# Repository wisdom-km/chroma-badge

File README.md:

# chroma-badge（BADGE-42C）：4.2 寸四色墨水屏 NFC 工牌

> **当前：** [状态](docs/06-current-status.md) · [交接](docs/03-handoff.md) · [流程](docs/09-process.md)（许可证 / CI / 贴胶 / 生产包）。2026-09-14 复审是**旧 564 段板**档案，不要当现板。

仓库：https://github.com/wisdom-km/chroma-badge

一块 **6.3 mm 厚**的电子工牌：4.2" 黑白红黄四色墨水屏 + ESP32-C3（Wi-Fi/BLE/原生 USB）+ ST25DV64KC NFC + ≤2 mm 超薄锂电 + USB-C。固件目前是 v0.2 上电自检；手机传图（F2）未写。

| 背面 PCB 渲染 | 外壳（FreeCAD） |
|---|---|
|  | 见 `hardware/enclosure/output/badge_assembly.step` |

## 在本地接着做

```bash
git clone https://github.com/wisdom-km/chroma-badge.git
cd chroma-badge
```

用 Cursor **打开这个文件夹**（本地 Agent）。根目录 `AGENTS.md` 和 `.cursor/rules/badge.mdc` 会带上约定。

## 仓库

- `LICENSE.md`：硬件 CERN-OHL-P-2.0，固件/脚本 MIT
- `AGENTS.md`：硬性约定与当前进度
- `docs/01-architecture-decisions.md`：选型
- `docs/02-bom-and-cost.md`：BOM；屏贴胶 3M 467MP
- `docs/03-handoff.md`：复现步骤与**当前板**指纹
- `docs/09-process.md`：CI、生产包、贴胶
- `hardware/pcb/`：由 `scripts/design.py` 生成
- `firmware/README.md`：v0.2 自检；不要覆盖 `output/badge-42c-v0.1*.bin`

## 快速开始

全量 ERC/DRC 需要 KiCad **10.0.6**。不要把 `gen_pcb.py` 当日常命令（会清布线）。日常检查：

```bash
cd hardware/pcb
python3 scripts/check_netlist.py
./scripts/export.sh --check-only
```

自动布线流程见 `docs/03-handoff.md` 第 3 节。

## 状态

**H2（2026-09-15）：** 58 封装，PCB **680 段 / 115 过孔**，J1.7 NC。KiCad 10.0.6 全量 ERC/DRC 0。USB **0.8 mm**。固件 **v0.2 F1**。没有生产 zip。

下一步：打样实机；F2 须选定一条传图路线。

## 第三方内容

- 乐鑫 KiCad 库（ESP32-C3-MINI-1）：CC-BY-SA 4.0
- HRO TYPE-C-31-M-14 封装：jenschr/USB-C-Connectors，公有领域
- 其余符号/封装来自 KiCad 官方库

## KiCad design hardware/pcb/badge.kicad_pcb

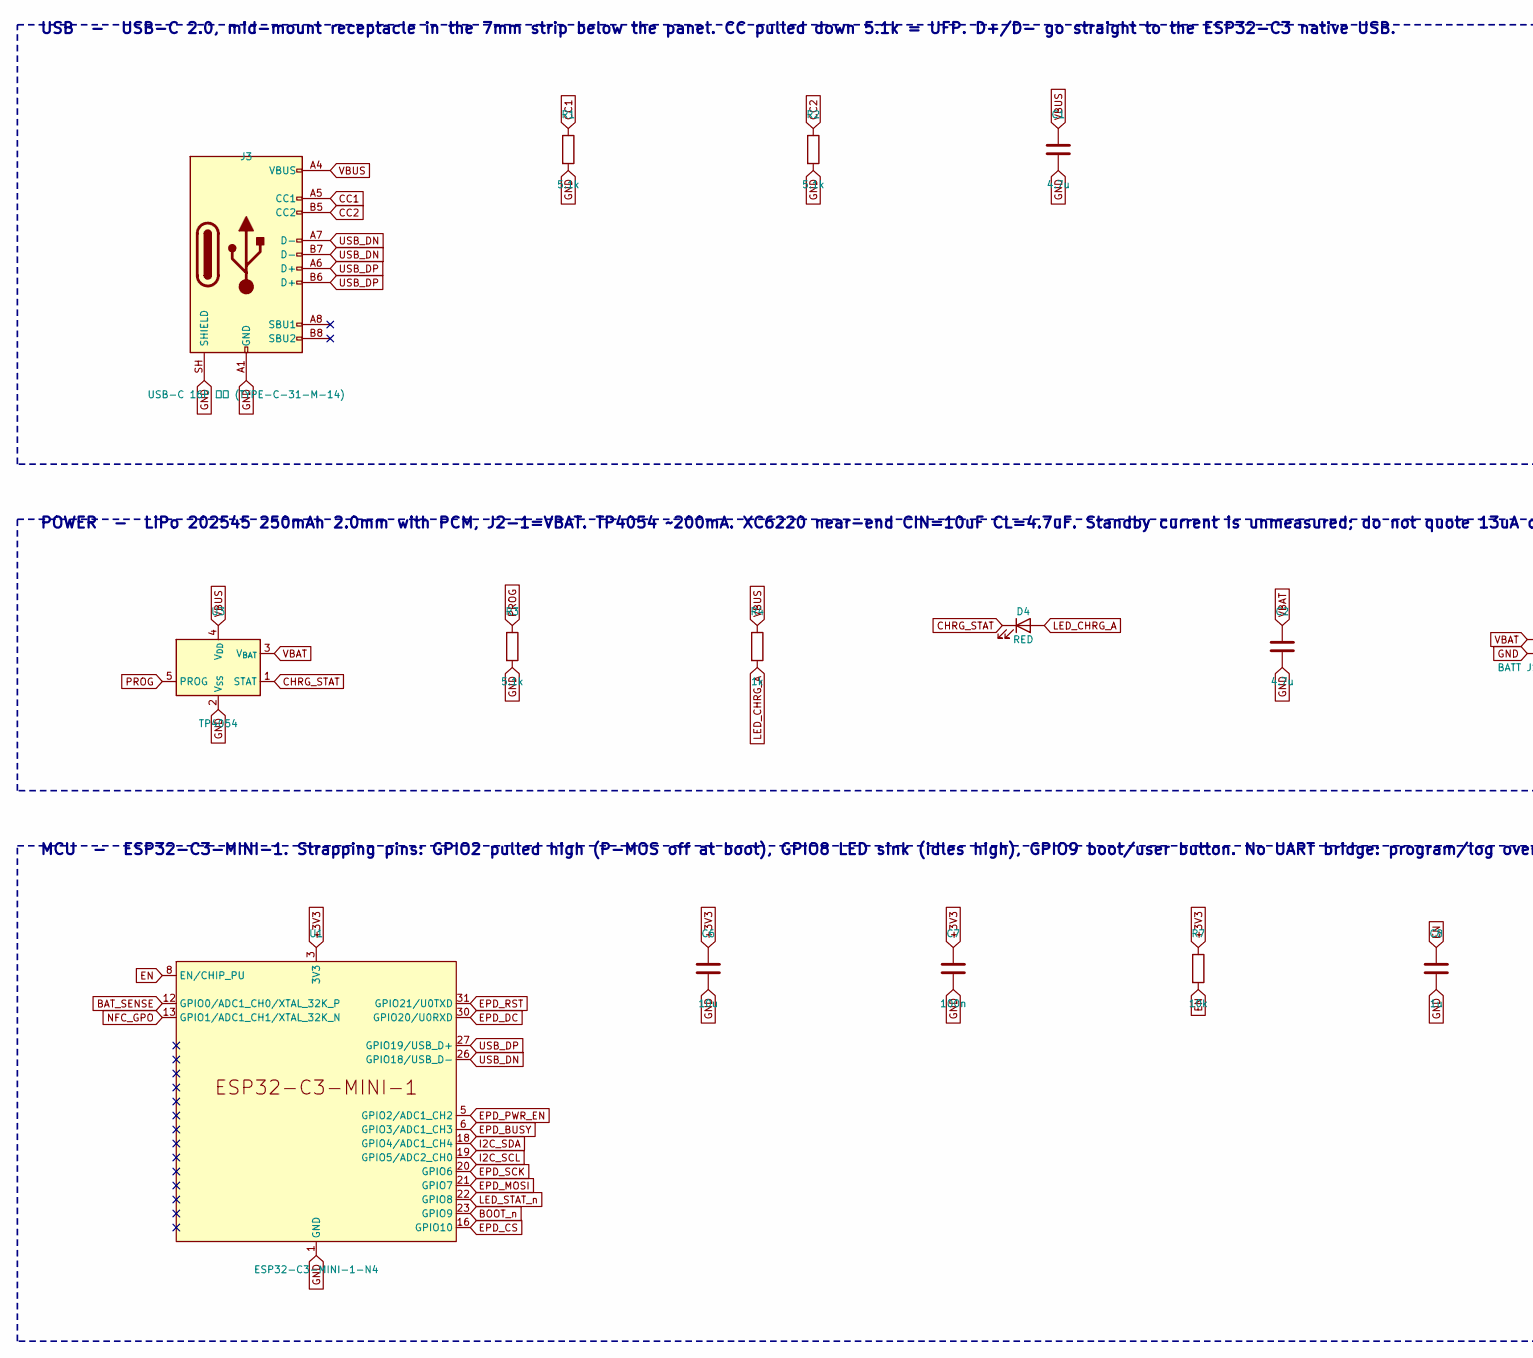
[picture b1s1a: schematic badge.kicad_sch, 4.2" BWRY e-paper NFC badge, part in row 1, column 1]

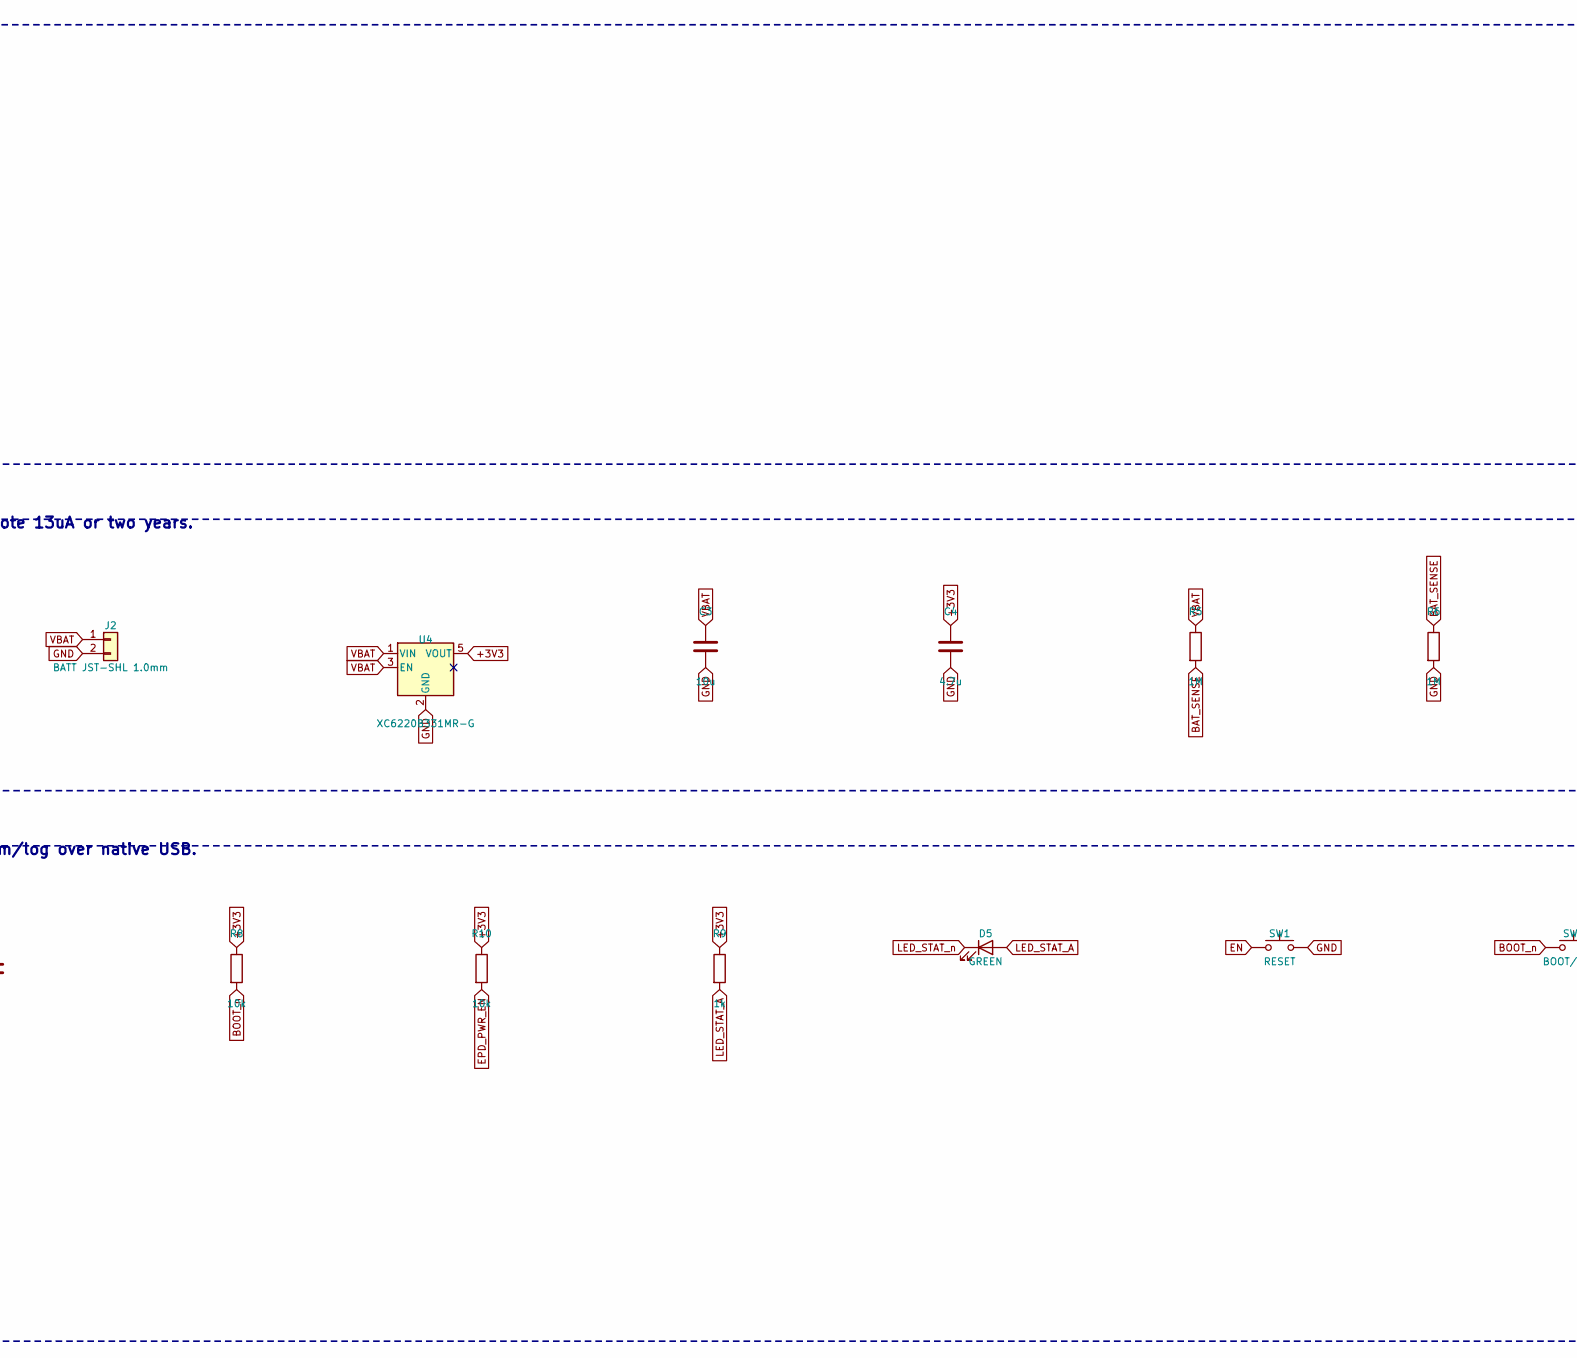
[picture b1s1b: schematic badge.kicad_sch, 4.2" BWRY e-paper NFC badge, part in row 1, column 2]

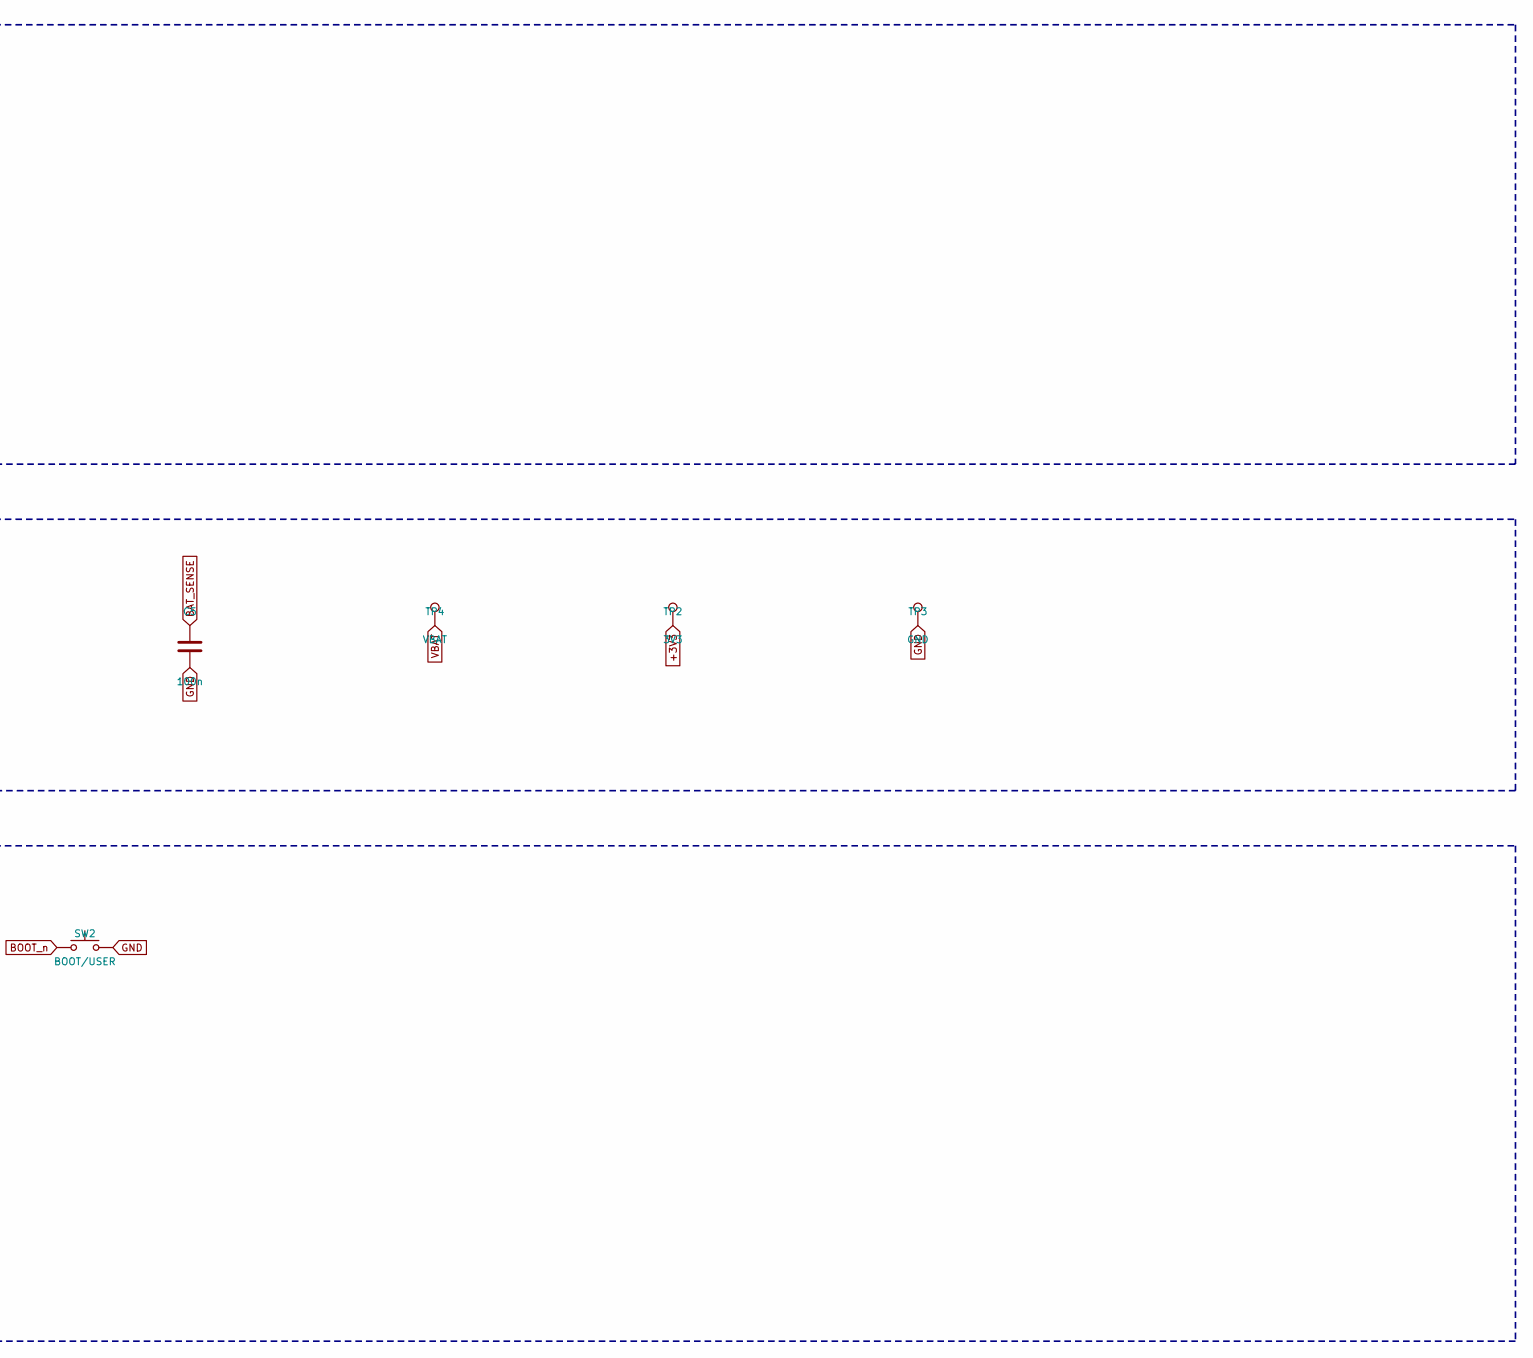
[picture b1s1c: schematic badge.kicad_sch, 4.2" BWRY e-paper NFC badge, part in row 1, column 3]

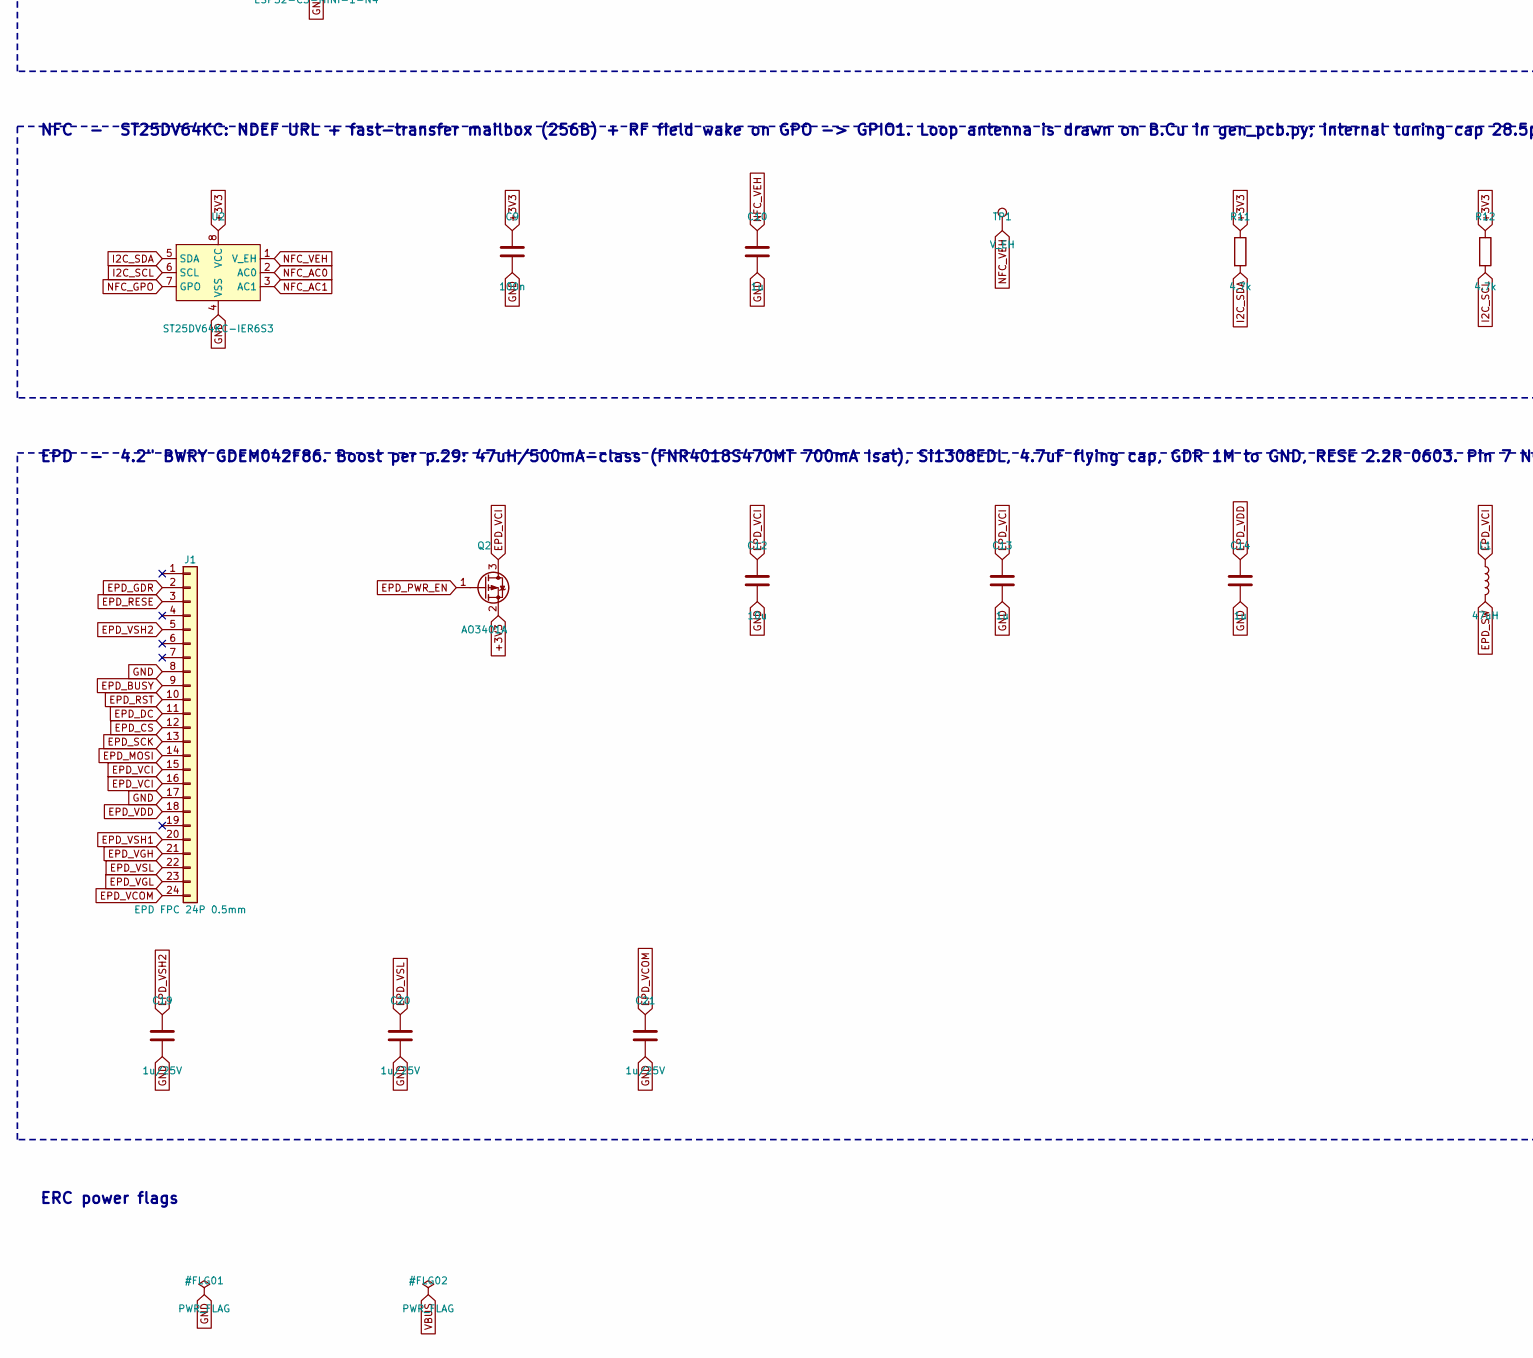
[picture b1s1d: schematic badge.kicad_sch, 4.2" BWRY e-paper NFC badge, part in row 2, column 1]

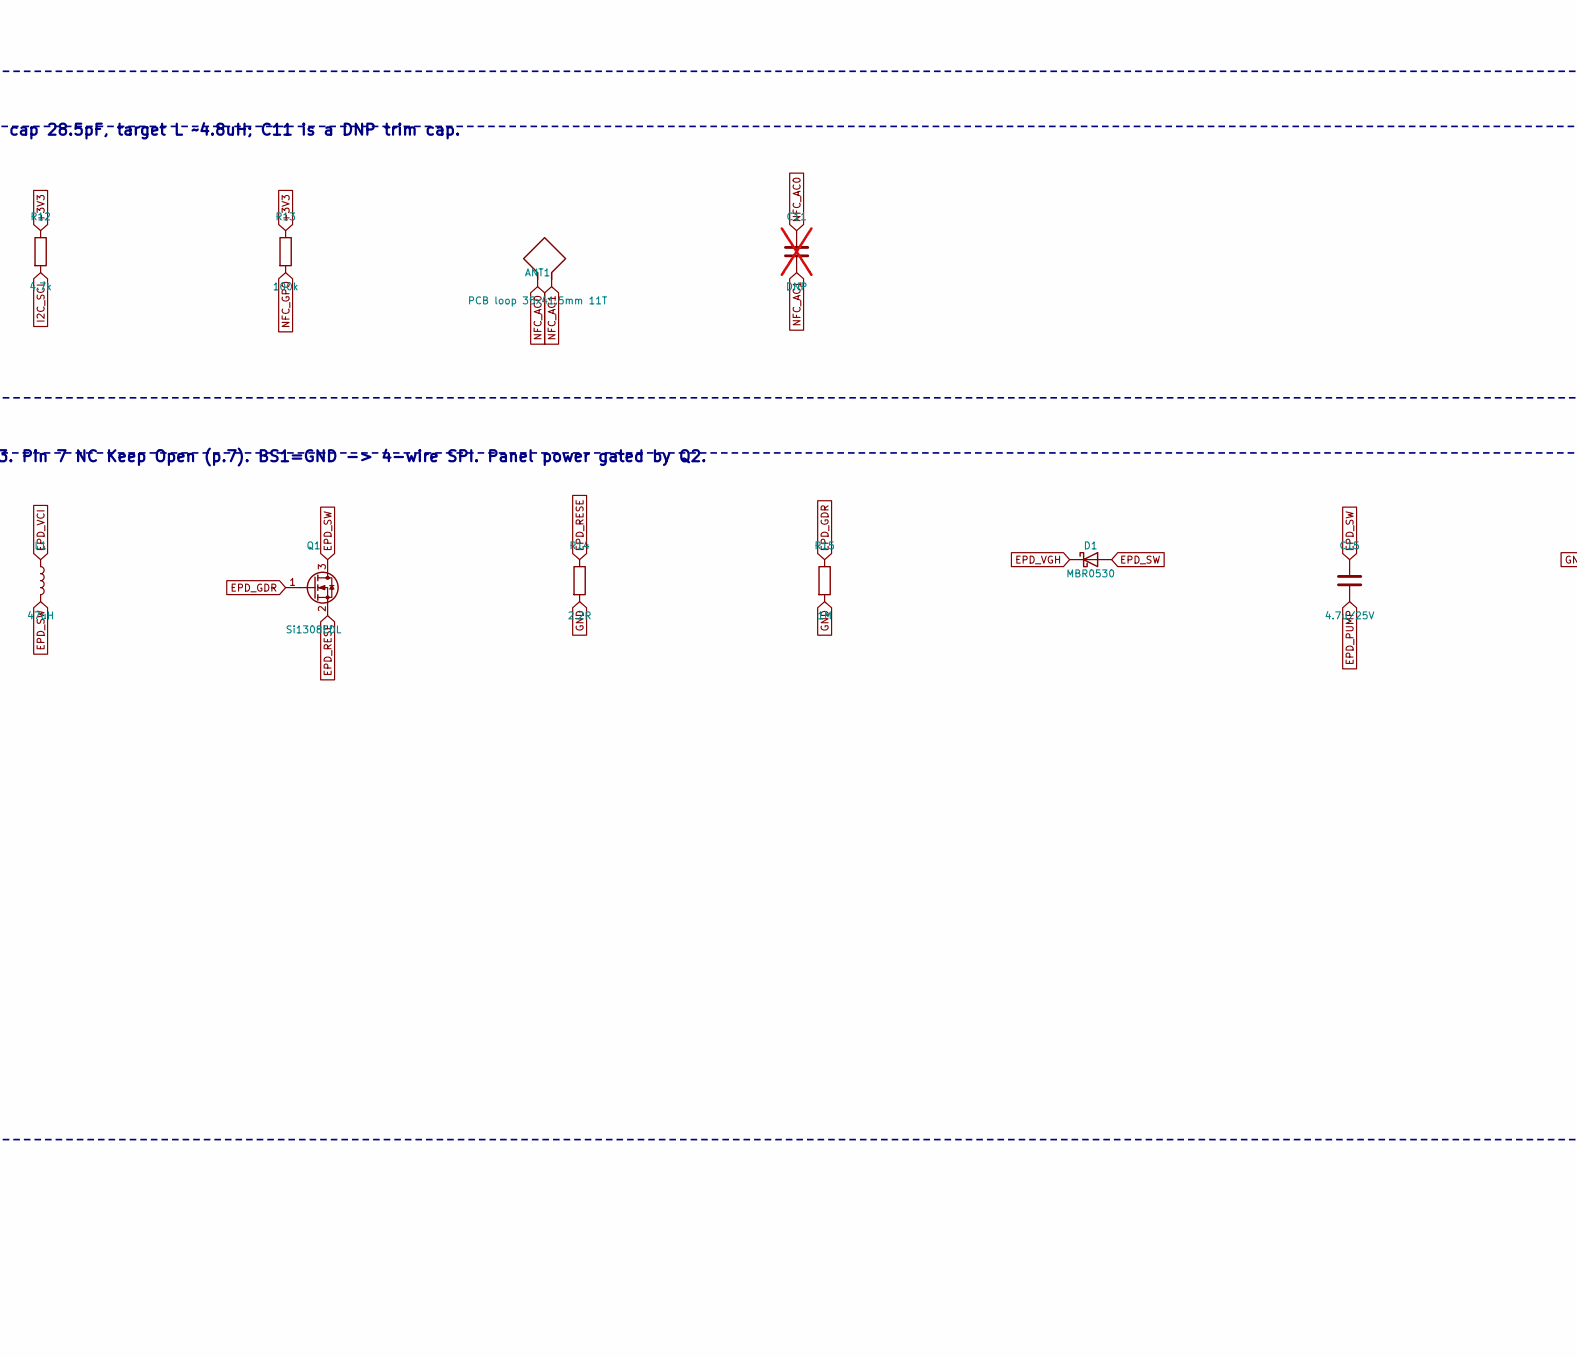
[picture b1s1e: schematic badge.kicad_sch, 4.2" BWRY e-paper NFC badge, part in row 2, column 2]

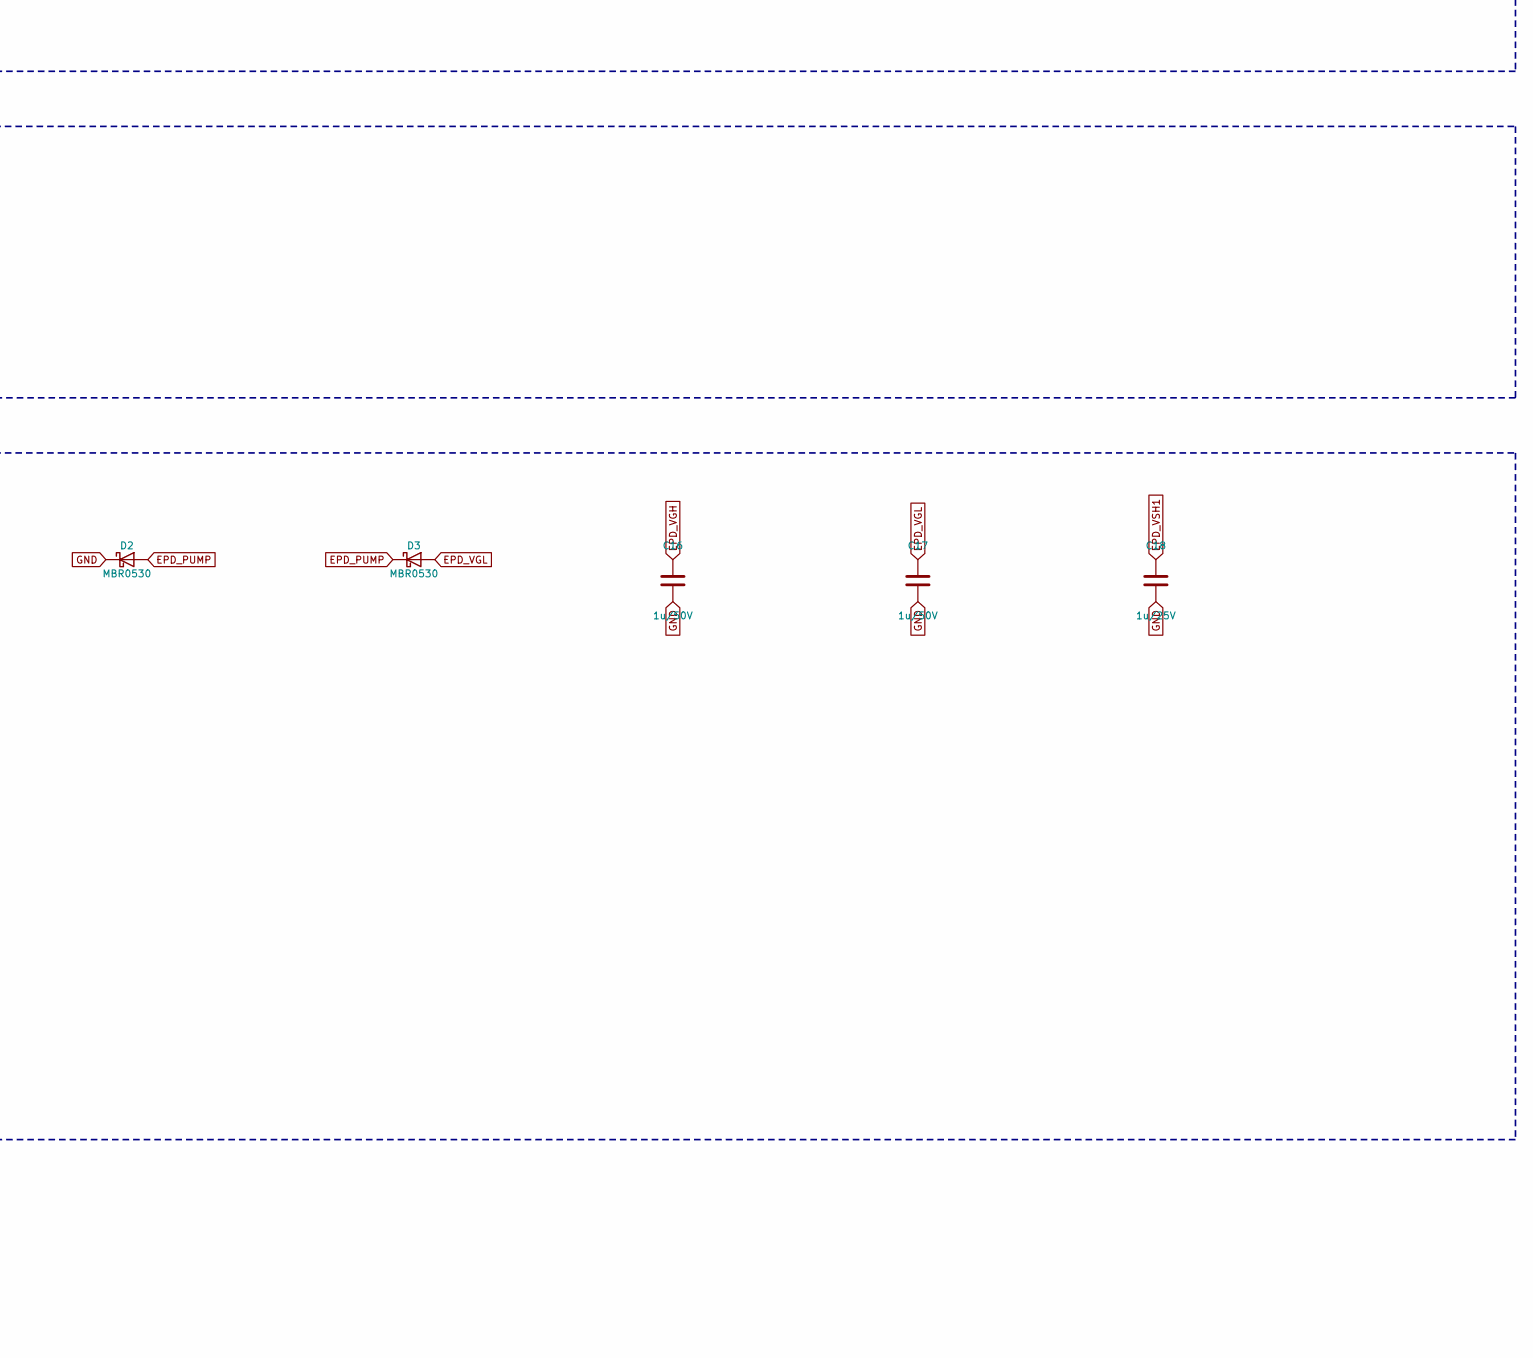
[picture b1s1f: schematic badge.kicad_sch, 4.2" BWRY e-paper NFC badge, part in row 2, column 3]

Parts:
ANT1: PCB loop 35x41.5mm 11T; NFC_Loop
C1, C2, C4: 4.7u; C_0603_1608Metric
C3, C6, C12: 10u; C_0603_1608Metric
C5, C7, C9: 100n; C_0402_1005Metric
C8, C10, C13, C14: 1u; C_0402_1005Metric
C11: DNP; C_0402_1005Metric; not fitted
C15: 4.7u/25V; C_0805_2012Metric
C16, C17: 1u/50V; C_0805_2012Metric
C18, C19, C20, C21: 1u/25V; C_0603_1608Metric
D1, D2, D3: MBR0530; D_SOD-123; LCSC C77896
D4: RED; LED_0603_1608Metric
D5: GREEN; LED_0603_1608Metric
J1: EPD FPC 24P 0.5mm; Hirose_FH12-24S-0.5SH_1x24-1MP_P0.50mm_Horizontal; LCSC C262657
J2: BATT JST-SHL 1.0mm; JST_SHL_SM02B-SHLS-TF_1x02-1MP_P1.00mm_Horizontal; LCSC C145956
J3: USB-C 16P 沉板 (TYPE-C-31-M-14); TYPE-C-31-M-14; LCSC C223907
L1: 47uH; L_Changjiang_FNR4018S; LCSC C167813
Q1: Si1308EDL; SOT-323_SC-70; LCSC C469327
Q2: AO3401A; SOT-23; LCSC C15127
R1, R2, R3: 5.1k; R_0402_1005Metric
R4, R9: 1k; R_0402_1005Metric
R5, R6, R15: 1M; R_0402_1005Metric
R7, R8, R10: 10k; R_0402_1005Metric
R11, R12: 4.7k; R_0402_1005Metric
R13: 100k; R_0402_1005Metric
R14: 2.2R; R_0603_1608Metric
SW1: RESET; SW_SPST_PTS810; LCSC C221929
SW2: BOOT/USER; SW_SPST_PTS810; LCSC C221929
TP1: V_EH; TestPoint_Pad_D1.0mm
TP2: 3V3; TestPoint_Pad_D1.0mm
TP3: GND; TestPoint_Pad_D1.0mm
TP4: VBAT; TestPoint_Pad_D1.0mm
U1: ESP32-C3-MINI-1-N4; ESP32-C3-MINI-1; LCSC C2934569
U2: ST25DV64KC-IER6S3; SOIC-8_3.9x4.9mm_P1.27mm; LCSC C2830253
U3: TP4054; SOT-23-5; LCSC C32574
U4: XC6220B331MR-G; SOT-23-5; LCSC C86534

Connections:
+3V3: C4.1, C6.1, C7.1, C9.1, Q2.2 (S), R7.1, R8.1, R9.1, R10.1, R11.1, R12.1, R13.1, TP2.1, U1.3 (3V3), U2.8 (VCC), U4.5 (VOUT)
BAT_SENSE: C5.1, R5.2, R6.1, U1.12 (GPIO0/ADC1_CH0/XTAL_32K_P)
BOOT_n: R8.2, SW2.1, U1.23 (GPIO9)
CC1: J3.A5 (CC1), R1.1
CC2: J3.B5 (CC2), R2.1
CHRG_STAT: D4.1 (K), U3.1 (STAT)
EN: C8.1, R7.2, SW1.1, U1.8 (EN/CHIP_PU)
EPD_BUSY: J1.9, U1.6 (GPIO3/ADC1_CH3)
EPD_CS: J1.12, U1.16 (GPIO10)
EPD_DC: J1.11, U1.30 (GPIO20/U0RXD)
EPD_GDR: J1.2, Q1.1 (G), R15.1
EPD_MOSI: J1.14, U1.21 (GPIO7)
EPD_PUMP: C15.2, D2.2 (A), D3.1 (K)
EPD_PWR_EN: Q2.1 (G), R10.2, U1.5 (GPIO2/ADC1_CH2)
EPD_RESE: J1.3, Q1.2 (S), R14.1
EPD_RST: J1.10, U1.31 (GPIO21/U0TXD)
EPD_SCK: J1.13, U1.20 (GPIO6)
EPD_SW: C15.1, D1.2 (A), L1.2, Q1.3 (D)
EPD_VCI: C12.1, C13.1, J1.15, J1.16, L1.1, Q2.3 (D)
EPD_VCOM: C21.1, J1.24
EPD_VDD: C14.1, J1.18
EPD_VGH: C16.1, D1.1 (K), J1.21
EPD_VGL: C17.1, D3.2 (A), J1.23
EPD_VSH1: C18.1, J1.20
EPD_VSH2: C19.1, J1.5
EPD_VSL: C20.1, J1.22
GND: C1.2, C2.2, C3.2, C4.2, C5.2, C6.2, C7.2, C8.2, C9.2, C10.2, C12.2, C13.2, C14.2, C16.2, C17.2, C18.2, C19.2, C20.2, C21.2, D2.1 (K), J1.8, J1.17, J2.2, J3.A1 (GND), J3.A12 (GND), J3.B1 (GND), J3.B12 (GND), J3.SH (SHIELD), R1.2, R2.2, R3.2, R6.2, R14.2, R15.2, SW1.2, SW2.2, TP3.1, U1.1 (GND), U1.2 (GND), U1.11 (GND), U1.14 (GND), U1.36 (GND), U1.37 (GND), U1.38 (GND), U1.39 (GND), U1.40 (GND), U1.41 (GND), U1.42 (GND), U1.43 (GND), U1.44 (GND), U1.45 (GND), U1.46 (GND), U1.47 (GND), U1.48 (GND), U1.49 (GND), U1.50 (GND), U1.51 (GND), U1.52 (GND), U1.53 (GND), U2.4 (VSS), U3.2 (V_{SS}), U4.2 (GND)
I2C_SCL: R12.2, U1.19 (GPIO5/ADC2_CH0), U2.6 (SCL)
I2C_SDA: R11.2, U1.18 (GPIO4/ADC1_CH4), U2.5 (SDA)
LED_CHRG_A: D4.2 (A), R4.2
LED_STAT_A: D5.2 (A), R9.2
LED_STAT_n: D5.1 (K), U1.22 (GPIO8)
NFC_AC0: ANT1.1, C11.1, U2.2 (AC0)
NFC_AC1: ANT1.2, C11.2, U2.3 (AC1)
NFC_GPO: R13.2, U1.13 (GPIO1/ADC1_CH1/XTAL_32K_N), U2.7 (GPO)
NFC_VEH: C10.1, TP1.1, U2.1 (V_EH)
PROG: R3.1, U3.5 (PROG)
USB_DN: J3.A7 (D-), J3.B7 (D-), U1.26 (GPIO18/USB_D-)
USB_DP: J3.A6 (D+), J3.B6 (D+), U1.27 (GPIO19/USB_D+)
VBAT: C2.1, C3.1, J2.1, R5.1, TP4.1, U3.3 (V_{BAT}), U4.1 (VIN), U4.3 (EN)
VBUS: C1.1, J3.A4 (VBUS), J3.A9 (VBUS), J3.B4 (VBUS), J3.B9 (VBUS), R4.1, U3.4 (V_{DD})

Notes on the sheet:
USB - USB-C 2.0, mid-mount receptacle in the 7mm strip below the panel. CC pulled down 5.1k = UFP. D+/D- go straight to the ESP32-C3 native USB.
POWER - LiPo 202545 250mAh 2.0mm with PCM, J2-1=VBAT. TP4054 ~200mA. XC6220 near-end CIN=10uF CL=4.7uF. Standby current is unmeasured; do not quote 13uA or two years.
MCU - ESP32-C3-MINI-1. Strapping pins: GPIO2 pulled high (P-MOS off at boot), GPIO8 LED sink (idles high), GPIO9 boot/user button. No UART bridge: program/log over native USB.
NFC - ST25DV64KC: NDEF URL + fast-transfer mailbox (256B) + RF field wake on GPO -> GPIO1. Loop antenna is drawn on B.Cu in gen_pcb.py; internal tuning cap 28.5pF, target L ~4.8uH; C11 is a DNP trim cap.
EPD - 4.2" BWRY GDEM042F86. Boost per p.29: 47uH/500mA-class (FNR4018S470MT 700mA Isat), Si1308EDL, 4.7uF flying cap, GDR 1M to GND, RESE 2.2R 0603. Pin 7 NC Keep Open (p.7). BS1=GND -> 4-wire SPI. Panel power gated by Q2.
ERC power flags

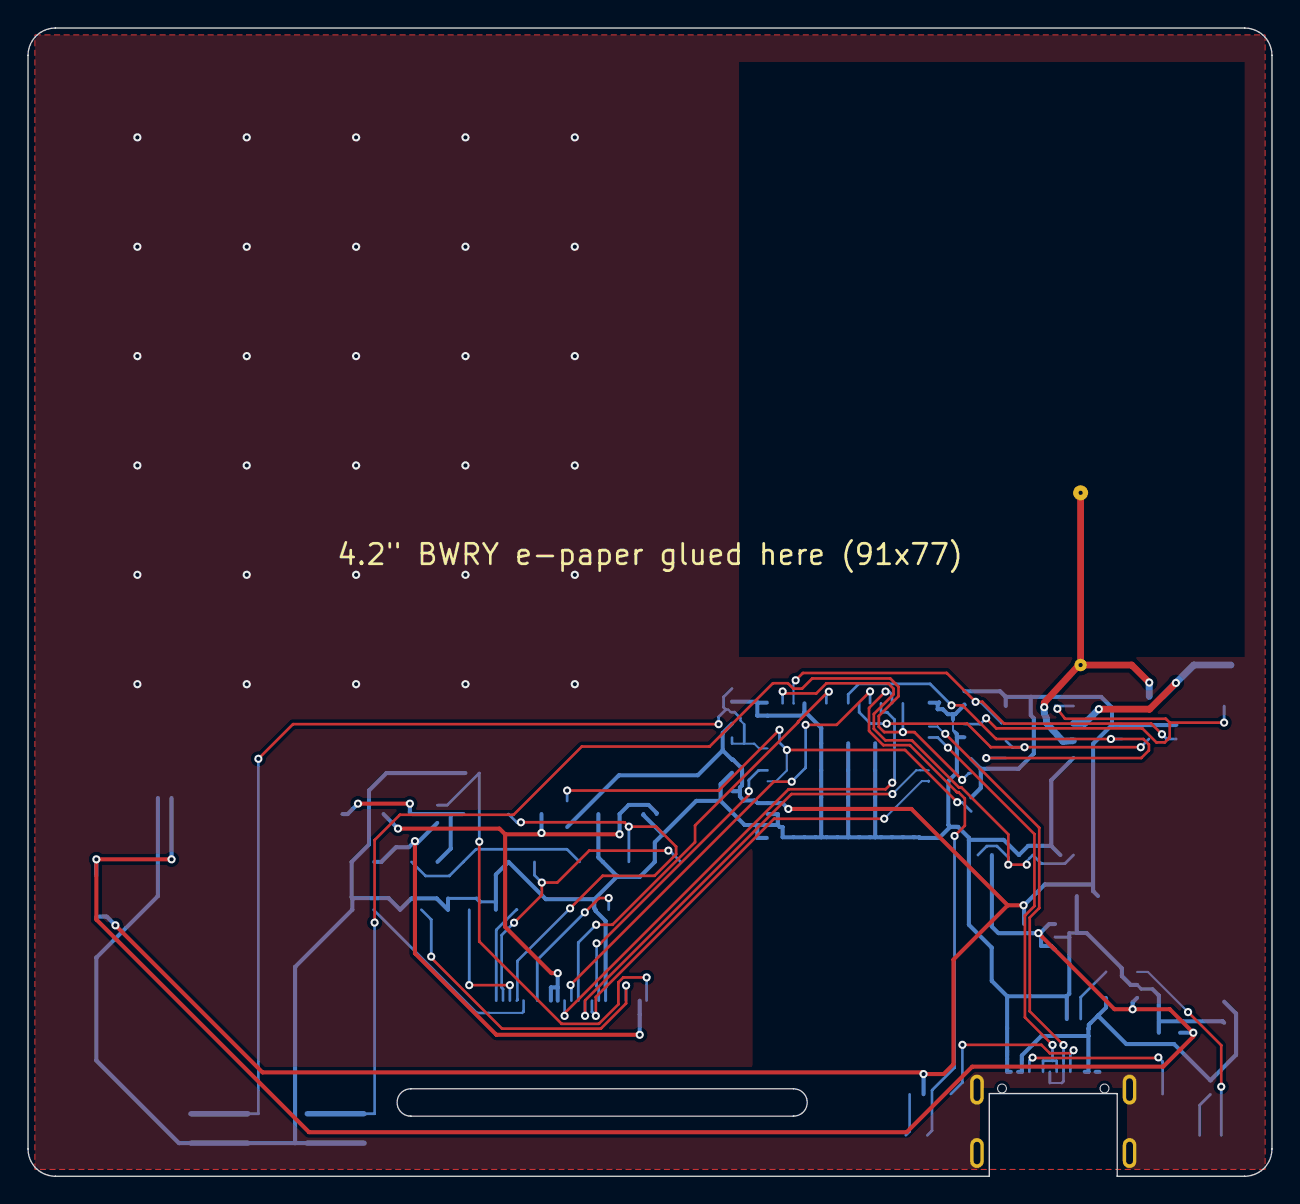
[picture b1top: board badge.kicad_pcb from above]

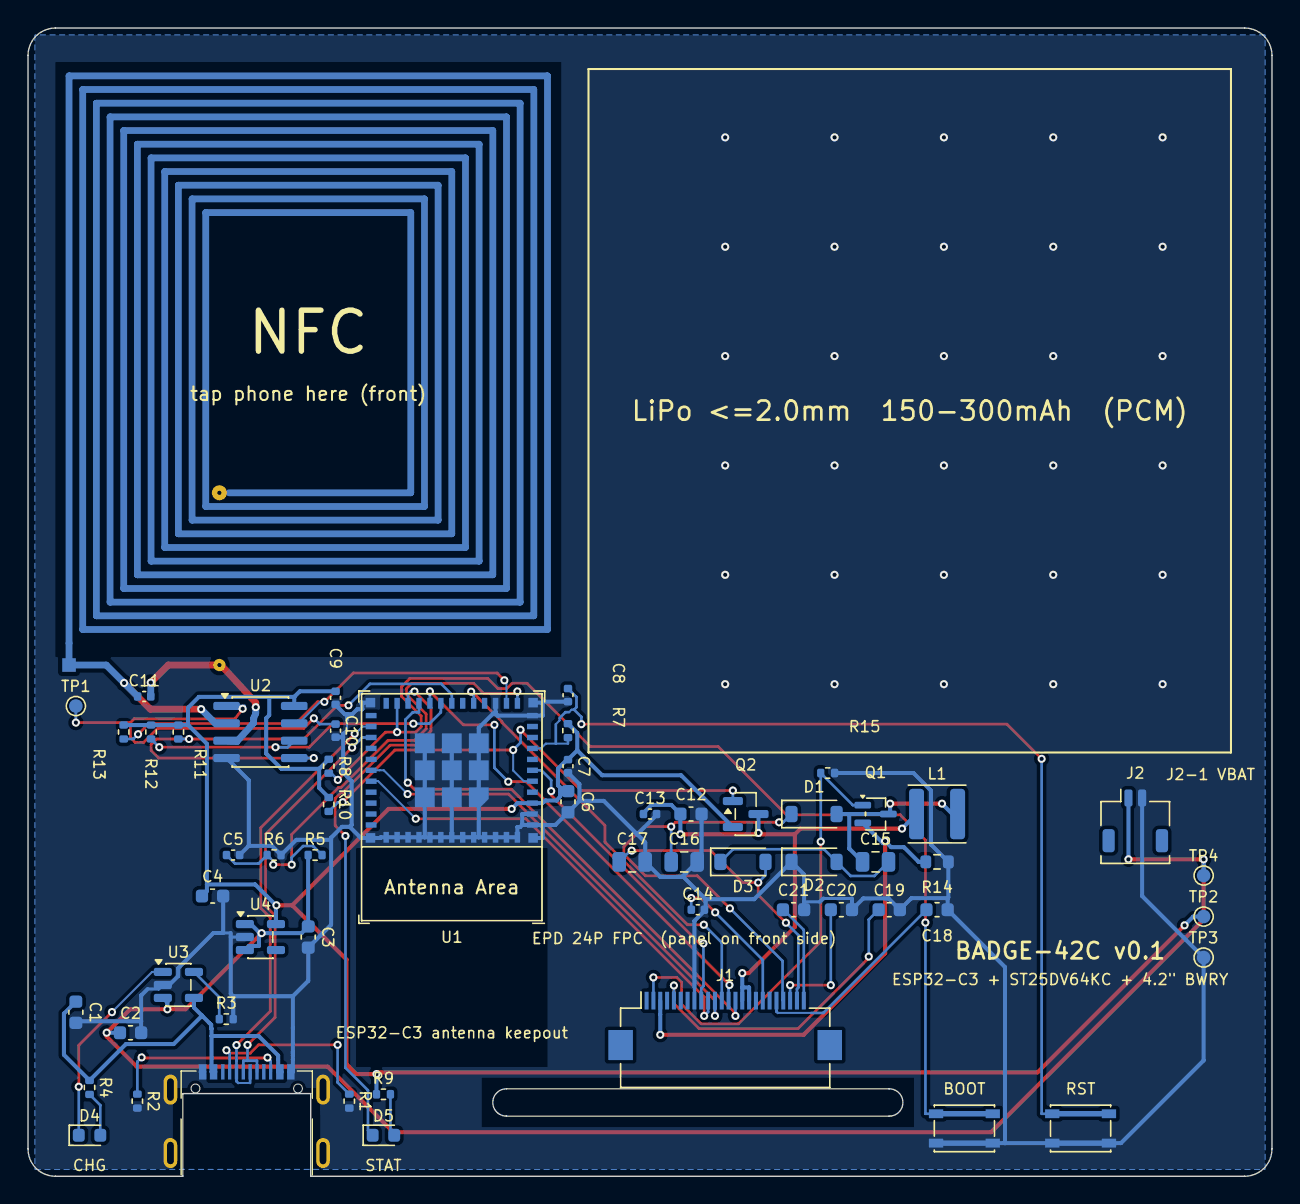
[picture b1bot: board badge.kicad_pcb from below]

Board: 2 copper layers, 91.0 x 84.0 mm, 58 parts (58 on the bottom side), 41 nets.

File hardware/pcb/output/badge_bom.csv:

"Ref","Value","Footprint","Description","LCSC","Qty","DNP"
"ANT1","PCB loop 35x41.5mm 11T","badge:NFC_Loop","PCB spiral antenna, net-tie footprint generated by gen_nfc_footprint.py; tune with C11","","1",""
"C1,C2","4.7u","Capacitor_SMD:C_0603_1608Metric","4.7uF 10V X5R 0603","","2",""
"C3,C8,C10,C13,C14","1u","Capacitor_SMD:C_0402_1005Metric","1u 0402","","5",""
"C4","2.2u","Capacitor_SMD:C_0603_1608Metric","2.2uF 10V 0603","","1",""
"C5,C7,C9","100n","Capacitor_SMD:C_0402_1005Metric","100n 0402","","3",""
"C6,C12","10u","Capacitor_SMD:C_0603_1608Metric","10uF 6.3V X5R 0603","","2",""
"C15-C17","1u/50V","Capacitor_SMD:C_0805_2012Metric","1uF 50V X7R 0805,1uF 50V X7R 0805 charge pump","","3",""
"C18-C21","1u/25V","Capacitor_SMD:C_0603_1608Metric","1uF 25V X7R 0603","","4",""
"D1-D3","MBR0530","Diode_SMD:D_SOD-123","Schottky 30V 0.5A SOD-123","C77896","3",""
"D4","RED","LED_SMD:LED_0603_1608Metric","LED 0603 red, charging indicator","","1",""
"D5","GREEN","LED_SMD:LED_0603_1608Metric","LED 0603 green, status","","1",""
"J1","EPD FPC 24P 0.5mm","Connector_FFC-FPC:Hirose_FH12-24S-0.5SH_1x24-1MP_P0.50mm_Horizontal","24P 0.5mm FPC connector, bottom contact, flip lock (Hirose FH12-24S-0.5SH or JUSHUO AFC07-S24FCA-00)","C262657","1",""
"J2","BATT JST-SH 1.0mm","Connector_JST:JST_SHL_SM02B-SHLS-TF_1x02-1MP_P1.00mm_Horizontal","JST SM02B-SHLS-TF 1.0mm 2P horizontal; LiPo <=2.0mm thick, 150-300mAh with PCM","C145956","1",""
"J3","USB-C 16P 沉板 (TYPE-C-31-M-14)","badge:TYPE-C-31-M-14","HRO TYPE-C-31-M-14, 16P USB 2.0 mid-mount receptacle","C223907","1",""
"L1","68uH","Inductor_SMD:L_Changjiang_FNR3015S","68uH shielded power inductor, Isat>=0.2A, h<=1.5mm (Sunlord SWPA3015S680MT / FNR3015S680MT)","C2827366","1",""
"Q1","AO3400A","Package_TO_SOT_SMD:SOT-23","N-MOSFET for EPD boost (alt. Si1304BDL SOT-323)","C20917","1",""
"Q2","AO3401A","Package_TO_SOT_SMD:SOT-23","P-MOSFET load switch for panel + boost","C15127","1",""
"R1-R3","5.1k","Resistor_SMD:R_0402_1005Metric","5.1k -> ~200mA charge current,5.1k 0402 1%","","3",""
"R4,R9","1k","Resistor_SMD:R_0402_1005Metric","1k 0402 1%","","2",""
"R5,R6","1M","Resistor_SMD:R_0402_1005Metric","1M 0402 1%","","2",""
"R7,R8,R10","10k","Resistor_SMD:R_0402_1005Metric","10k 0402 1%","","3",""
"R11,R12","4.7k","Resistor_SMD:R_0402_1005Metric","4.7k 0402 1%","","2",""
"R13","100k","Resistor_SMD:R_0402_1005Metric","100k 0402 1%","","1",""
"R14","2.2R","Resistor_SMD:R_0402_1005Metric","RESE current-sense resistor: confirm value from GDEM042F86 spec (0.47R / 2.2R / 3R variants)","","1",""
"SW1","RESET","Button_Switch_SMD:SW_SPST_PTS810","C&K PTS810 low-profile tactile 1.5mm","C221929","1",""
"SW2","BOOT/USER","Button_Switch_SMD:SW_SPST_PTS810","C&K PTS810 low-profile tactile 1.5mm","C221929","1",""
"TP1","V_EH","TestPoint:TestPoint_Pad_D1.0mm","test pad (energy harvesting output)","","1",""
"TP2","3V3","TestPoint:TestPoint_Pad_D1.0mm","test pad","","1",""
"TP3","GND","TestPoint:TestPoint_Pad_D1.0mm","test pad","","1",""
"TP4","VBAT","TestPoint:TestPoint_Pad_D1.0mm","test pad","","1",""
"U1","ESP32-C3-MINI-1-N4","badge:ESP32-C3-MINI-1","Espressif ESP32-C3-MINI-1-N4 Wi-Fi/BLE module, 13.2x16.6x2.4mm","C2934569","1",""
"U2","ST25DV64KC-IER6S3","Package_SO:SOIC-8_3.9x4.9mm_P1.27mm","ST25DV64KC dynamic NFC tag, 64Kbit, FTM mailbox, energy harvesting, SO8N","C2830253","1",""
"U3","TP4054 / MCP73831T-2ACI/OT","Package_TO_SOT_SMD:SOT-23-5","Li-ion linear charger 4.2V, SOT-23-5 (TP4054 pin-compatible)","C32574","1",""
"U4","XC6220B331MR-G","Package_TO_SOT_SMD:SOT-23-5","LDO 3.3V, Iq 8uA, 1A, SOT-25 (pinout VIN/GND/CE/NC/VOUT). Alt: TLV75533PDBV, AP2112K-3.3","C86534","1",""

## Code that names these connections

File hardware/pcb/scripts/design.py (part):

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    Part("U1", "Espressif", "ESP32-C3-MINI-1", "badge:ESP32-C3-MINI-1", "ESP32-C3-MINI-1-N4",
         {**{str(p): "GND" for p in [1, 2, 11, 14] + list(range(36, 54))},
          "3": "+3V3", "8": "EN",
          "12": "BAT_SENSE",      # GPIO0 / ADC1_CH0
          "13": "NFC_GPO",        # GPIO1  (RTC wake)
          "5": "EPD_PWR_EN",      # GPIO2  strapping: pulled high, P-MOS off by default
          "6": "EPD_BUSY",        # GPIO3
          "18": "I2C_SDA",        # GPIO4
          "19": "I2C_SCL",        # GPIO5
          "20": "EPD_SCK",        # GPIO6
          "21": "EPD_MOSI",       # GPIO7
          "22": "LED_STAT_n",     # GPIO8  strapping: LED sink, idles high
          "23": "BOOT_n",         # GPIO9  strapping: boot button / user button
          "16": "EPD_CS",         # GPIO10
          "26": "USB_DN",         # GPIO18
          "27": "USB_DP",         # GPIO19
          "30": "EPD_DC",         # GPIO20
          "31": "EPD_RST"},       # GPIO21
         nc=[str(p) for p in [4, 7, 9, 10, 15, 17, 24, 25, 28, 29, 32, 33, 34, 35]],
         section="MCU", desc="Espressif ESP32-C3-MINI-1-N4 Wi-Fi/BLE module, 13.2x16.6x2.4mm", lcsc="C2934569",
         at=(60.0, 57.0, 180)),
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SECTION_NOTES = {
    "USB": "USB-C 2.0, mid-mount receptacle in the 7mm strip below the panel. CC pulled down 5.1k = UFP. D+/D- go straight to the ESP32-C3 native USB.",
    "POWER": "LiPo 202545 250mAh 2.0mm with PCM, J2-1=VBAT. TP4054 ~200mA. XC6220 near-end CIN=10uF CL=4.7uF. Standby current is unmeasured; do not quote 13uA or two years.",
    "MCU": "ESP32-C3-MINI-1. Strapping pins: GPIO2 pulled high (P-MOS off at boot), GPIO8 LED sink (idles high), GPIO9 boot/user button. No UART bridge: program/log over native USB.",
    "NFC": "ST25DV64KC: NDEF URL + fast-transfer mailbox (256B) + RF field wake on GPO -> GPIO1. Loop antenna is drawn on B.Cu in gen_pcb.py; internal tuning cap 28.5pF, target L ~4.8uH; C11 is a DNP trim cap.",
    "EPD": "4.2\" BWRY GDEM042F86. Boost per p.29: 47uH/500mA-class (FNR4018S470MT 700mA Isat), Si1308EDL, 4.7uF flying cap, GDR 1M to GND, RESE 2.2R 0603. Pin 7 NC Keep Open (p.7). BS1=GND -> 4-wire SPI. Panel power gated by Q2.",
}

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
